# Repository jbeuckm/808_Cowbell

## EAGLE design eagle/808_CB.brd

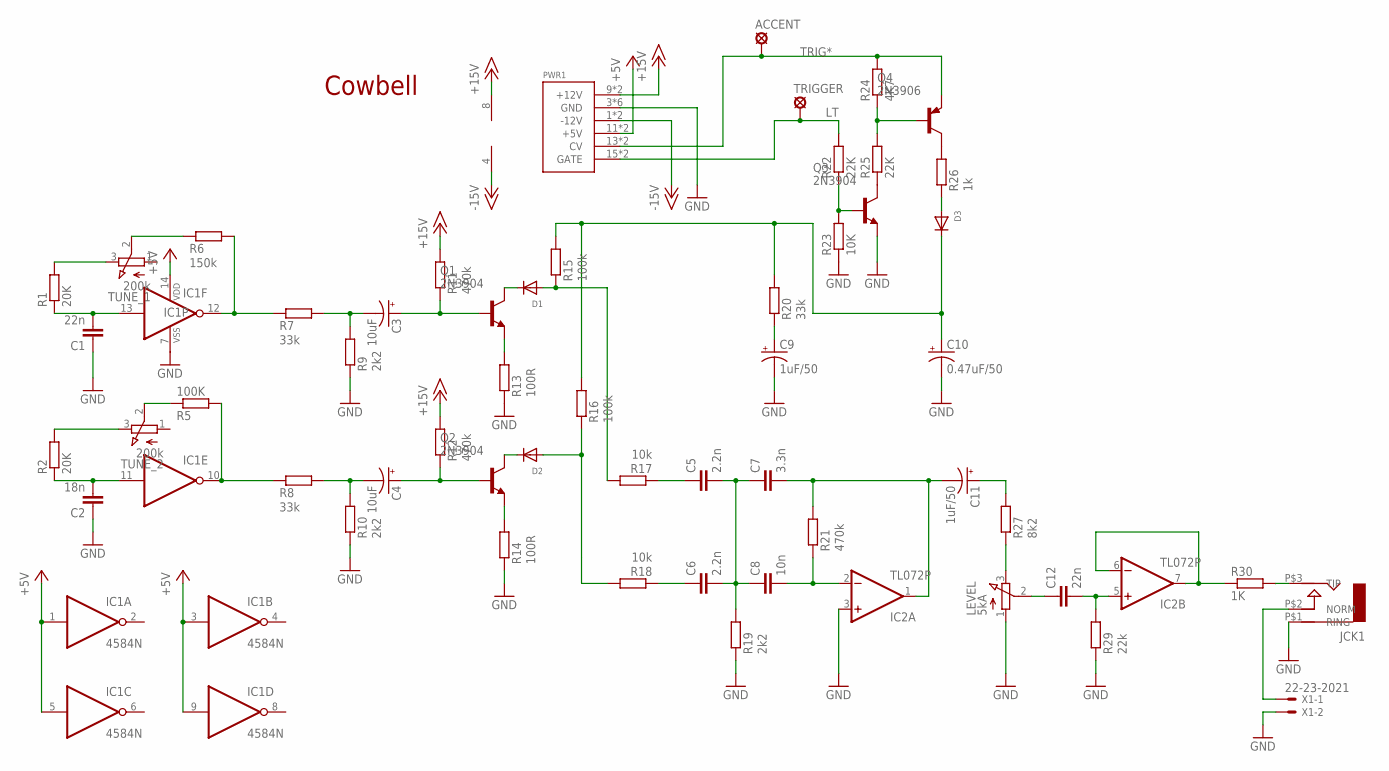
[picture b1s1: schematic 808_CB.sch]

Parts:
ACCENT: LSP11
C1: 22n; C035-030X60
C2: 18n; C035-030X60
C3, C4: 10uF; B45181A
C5, C6: 2.2n; C035-025X75
C7: 3.3n; C035-025X75
C8: 10n; C035-025X75
C9, C11: 1uF/50; B45181A
C10: 0.47uF/50; B45181A
C12: 22n; C035-025X75
D1, D2, D3: DIODEDO-1N4148; DO-1N4148
IC1: 4584N; DIL14
IC2: TL072P; DIL08
JCK1: AUDIO-JACK; ERTHENVAR-JACK-90DEG
LEVEL: 5kA; 3RP/1610N
PWR1: POWER; POWER_16
Q1, Q2, Q3: 2N3904; TO92
Q4: 2N3906; TO92
R1, R2: 20K; 0207/5V
R5: 100K; 0207/5V
R6: 150k; 0207/5V
R7, R20: 33k; 0207/5V
R8: 33k; 0207/7
R9, R10, R19: 2k2; 0207/5V
R11, R12, R21: 470k; 0207/5V
R13, R14: 100R; 0207/5V
R15, R16: 100k; 0207/5V
R17, R18: 10k; 0207/5V
R22, R25: 22K; 0207/5V
R23: 10K; 0207/5V
R24: 4K7; 0207/5V
R26: 1k; 0207/5V
R27: 8k2; 0207/5V
R29: 22k; 0207/5V
R30: 1K; 0207/5V
TRIGGER: LSP11
TUNE_1, TUNE_2: 200k; 3RP/1610N
X1: 22-23-2021

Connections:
+5V: IC1.1 (I), IC1.3 (I), IC1.5 (I), IC1.9 (I), IC1.14 (VDD), PWR1.11 (+5V), PWR1.12 (+5V)
+15V: IC2.8 (V+), PWR1.9 (+12V), PWR1.10 (+12V), R11.2, R12.2
-15V: IC2.4 (V-), PWR1.1 (-12V), PWR1.2 (-12V)
CY_OUT: JCK1.P$3 (TIP), R30.2
GND: C1.P$1 (1), C2.P$1 (1), C9.-, C10.-, IC1.7 (VSS), IC2.3 (+IN), JCK1.P$1 (RING), LEVEL.1 (A), PWR1.3 (GND), PWR1.4 (GND), PWR1.5 (GND), PWR1.6 (GND), PWR1.7 (GND), PWR1.8 (GND), Q3.3 (E), R9.1, R10.1, R13.1, R14.1, R19.1, R23.1, R29.1, X1.2
LT: PWR1.15 (GATE), PWR1.16 (GATE), R22.2, TRIGGER.MP
unnamed: C2.P$2 (2), IC1.11 (I), R2.1
unnamed: C1.P$2 (2), IC1.13 (I), R1.1
unnamed: Q3.1 (C), R25.1
unnamed: R5.1, TUNE_2.2 (S)
unnamed: R6.1, TUNE_1.2 (S)
unnamed: IC1.12 (O), R6.2, R7.1
unnamed: R1.2, TUNE_1.3 (E)
unnamed: R2.2, TUNE_2.3 (E)
unnamed: C4.-, R8.2, R10.2
unnamed: C3.-, R7.2, R9.2
unnamed: C4.+, Q2.2 (B), R12.1
unnamed: C3.+, Q1.2 (B), R11.1
unnamed: Q1.3 (E), R13.2
unnamed: Q2.3 (E), R14.2
unnamed: D2.C, Q2.1 (C)
unnamed: D1.C, Q1.1 (C)
unnamed: C10.+, D3.C, R15.2, R16.2, R20.2
unnamed: Q4.1 (C), R26.2
unnamed: D3.A, R26.1
unnamed: C9.+, R20.1
unnamed: D2.A, R16.1, R18.2
unnamed: D1.A, R15.1, R17.2
unnamed: C5.P$1 (1), R17.1
unnamed: C6.P$1 (1), R18.1
unnamed: C5.P$2 (2), C6.P$2 (2), C7.P$1 (1), C8.P$1 (1), R19.2
unnamed: C8.P$2 (2), IC2.2 (-IN), R21.1
unnamed: C7.P$2 (2), C11.-, IC2.1 (OUT), R21.2
unnamed: JCK1.P$2 (NORM), X1.1
unnamed: LEVEL.3 (E), R27.1
unnamed: C11.+, R27.2
unnamed: C12.P$1 (1), LEVEL.2 (S)
unnamed: C12.P$2 (2), IC2.5 (+IN), R29.2
unnamed: IC2.6 (-IN), IC2.7 (OUT), R30.1
unnamed: Q4.2 (B), R24.1, R25.2
unnamed: Q3.2 (B), R22.1, R23.2
TP7: IC1.10 (O), R5.2, R8.1
TRIG*: ACCENT.MP, PWR1.13 (CV), PWR1.14 (CV), Q4.3 (E), R24.2

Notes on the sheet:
Cowbell

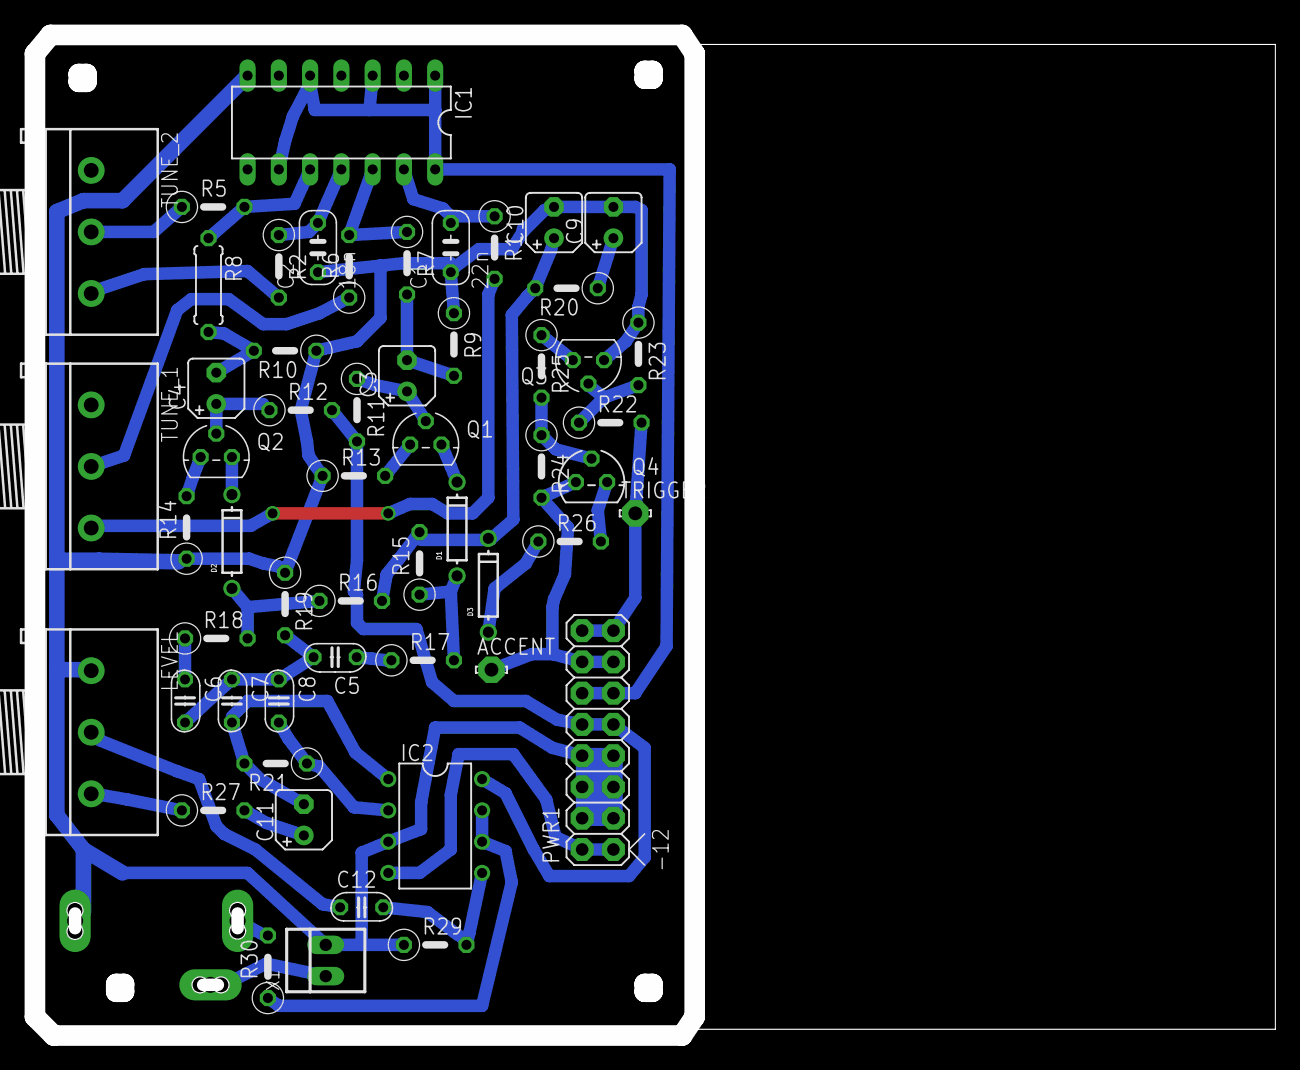
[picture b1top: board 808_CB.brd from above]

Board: 2 copper layers, 99.9 x 81.3 mm, 56 parts (0 on the bottom side), 43 nets.

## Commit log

2016-04-19 starting board part by part
2016-04-19 part by part
2016-04-19 parts on the board
2016-04-20 routed
2016-04-20 thicker traces
2016-04-20 trigger and accent pads
2016-04-20 tweaks and cleanups
2016-04-20 tweak
2016-04-21 switch back oscillator caps
